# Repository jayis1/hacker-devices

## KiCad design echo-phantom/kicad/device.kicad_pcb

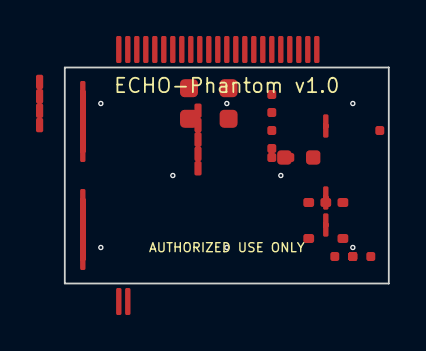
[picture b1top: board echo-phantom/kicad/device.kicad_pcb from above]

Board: 4 copper layers, 18.0 x 12.0 mm, 12 parts (0 on the bottom side), 19 nets, no tracks yet.

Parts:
C1: 100nF; C_0402_1005Metric
C2: 10uF; C_0603_1608Metric
D1: Red; LED_0402_1005Metric
D2: Blue; LED_0402_1005Metric
J1: Target I²S; Hirose_FH12-6S-0.5SH_1x06-1MP_P0.50mm_Horizontal
J2: Host I²S; Hirose_FH12-6S-0.5SH_1x06-1MP_P0.50mm_Horizontal
J3: USB-C; USB_C_Receptacle_GCT_USB4105
U1: STM32H743VIT6; LQFP-100_14x14mm_P0.5mm
U2: BT840F; Fanstel_BT840F
U3: IS42S16160G; TSOP-II-54_10.16x22.22mm_P0.8mm
U4: TLV75533; SOT-23-5
Y1: 25 MHz; Crystal_SMD_3225-4Pin_3.2x2.5mm

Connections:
BLE_RX: U1.PA10, U2.UART_TX
BLE_TX: U1.PA9, U2.UART_RX
FMC_D0: U1.PD14, U3.DQ0
FMC_D1: U1.PD15, U3.DQ1
GND: C1.2, C2.2, D1.2, D2.2, J1.5, J2.5, J3.A1, J3.B12, U1.2, U1.VSS1, U2.GND, U3.VSS1, U4.2, Y1.3
LED_BLUE: D2.1, U1.PB1
LED_RED: D1.1, U1.PB0
SAI1_BCLK_H: J2.1, U1.PB10
SAI1_BCLK_T: J1.1, U1.PA8
SAI1_MCLK_H: J2.4, U1.PC14
SAI1_MCLK_T: J1.4, U1.PC7
SAI1_SD_H: J2.3, U1.PE6
SAI1_SD_T: J1.3, U1.PB3
SAI1_WS_H: J2.2, U1.PF4
SAI1_WS_T: J1.2, U1.PA7
USB_DM: J3.A7, U1.PA11
USB_DP: J3.A6, U1.PA12
VBUS: J3.A4, J3.B9, U4.1, U4.3
VCC_3V3: C1.1, C2.1, J1.6, J2.6, U1.1, U1.VDD1, U2.VDD, U3.VDD1, U4.4, U4.5

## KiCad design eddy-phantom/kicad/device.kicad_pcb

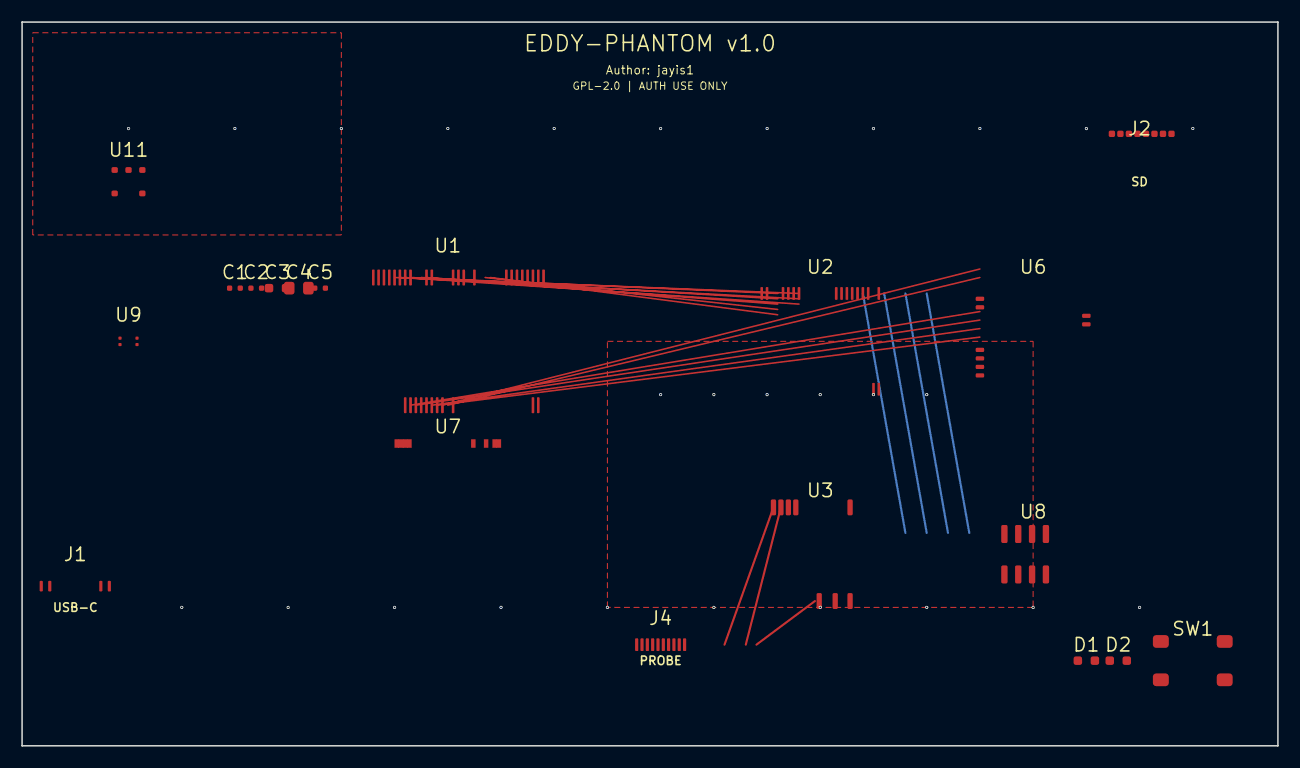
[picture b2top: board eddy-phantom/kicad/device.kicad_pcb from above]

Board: 2 copper layers, 118.0 x 68.0 mm, 19 parts (0 on the bottom side), 28 nets.

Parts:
C1, C2, C5: 100nF; C_0402_1005Metric
C3: 4.7uF; C_0603_1608Metric
C4: 10uF; C_0805_2012Metric
D1: LED_STATUS; LED_0603_1608Metric
D2: LED_CAPTURE; LED_0603_1608Metric
J1: USB-C; USB_C_Receptacle_HRO_TYPE-C-31-M-12
J2: Micro_SD; microSD_HC_Hirose_DM3AT-SF-PEJ521
J4: PROBE_ARRAY; Hirose_FH12-10S-0.5SH
SW1: BTN_ARM; SW_Push_SPST_SKQG_WithStem
U1: STM32H743VIT6; LQFP-100_14x14mm_P0.5mm
U2: AD7606C-6; LQFP-64_10x10mm_P0.5mm
U3: AD8331; SOIC-16_3.9x9.9mm_P1.27mm
U6: NINA-B306; ublox_NINA-B3
U7: IS42S32800G; TSOP-II-54_10.16x22.22mm_P0.8mm
U8: W25Q128JVSIQ; SOIC-8_3.9x4.9mm_P1.27mm
U9: TPS62743; VQFN-8_1.5x1.5mm_P0.4mm
U11: MCP73831; SOT-23-5

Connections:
+3V3: C1.1, C2.1, C3.1, J2.5, U1.1, U1.3, U2.40, U6.1, U7.1, U8.7, U8.8, U9.3
ADC_BUSY: U1.26, U2.27
ADC_CONVST: U1.18, U2.26
ADC_CS_N: U1.16, U2.25
ADC_RANGE: U1.27, U2.30
ADC_RST_N: U1.17, U2.28
AGND: C5.2, J4.2, J4.4, J4.6, J4.8, J4.10, U2.1, U3.2, U3.16
AVDD: C5.1, J4.9, U2.2, U3.3, U3.8
BLE_BOOT: U1.61, U6.24
BLE_CTS: U1.58, U6.11
BLE_RESET_N: U1.60, U6.23
BLE_RTS: U1.59, U6.12
BTN_ARM: SW1.1, SW1.3, U1.30
GND: C1.2, C2.2, C3.2, C4.2, D1.2, D2.2, J1.A1, J1.B1, J2.4, SW1.2, SW1.4, U1.2, U1.4, U2.41, U6.2, U7.2, U8.4, U9.2, U9.4, U11.2
LED_CAPTURE: D2.1, U1.29
LED_STATUS: D1.1, U1.28
PROBE_1_IN: J4.1, U3.1
PROBE_2_IN: J4.3, U3.14
QSPI_NCS: U1.39, U8.1
SPI1_MISO: U1.6, U2.23
SPI1_MOSI: U1.7, U2.24
SPI1_SCK: U1.5, U2.22
SPI4_MOSI: J2.1, J2.2, J2.3
SPI4_SCK: J2.6, U1.8
USART3_RX: U1.57, U6.10
USART3_TX: U1.56, U6.9
VBAT: C4.1, U9.1, U11.3
VUSB: J1.A4, J1.B4, U11.4, U11.5

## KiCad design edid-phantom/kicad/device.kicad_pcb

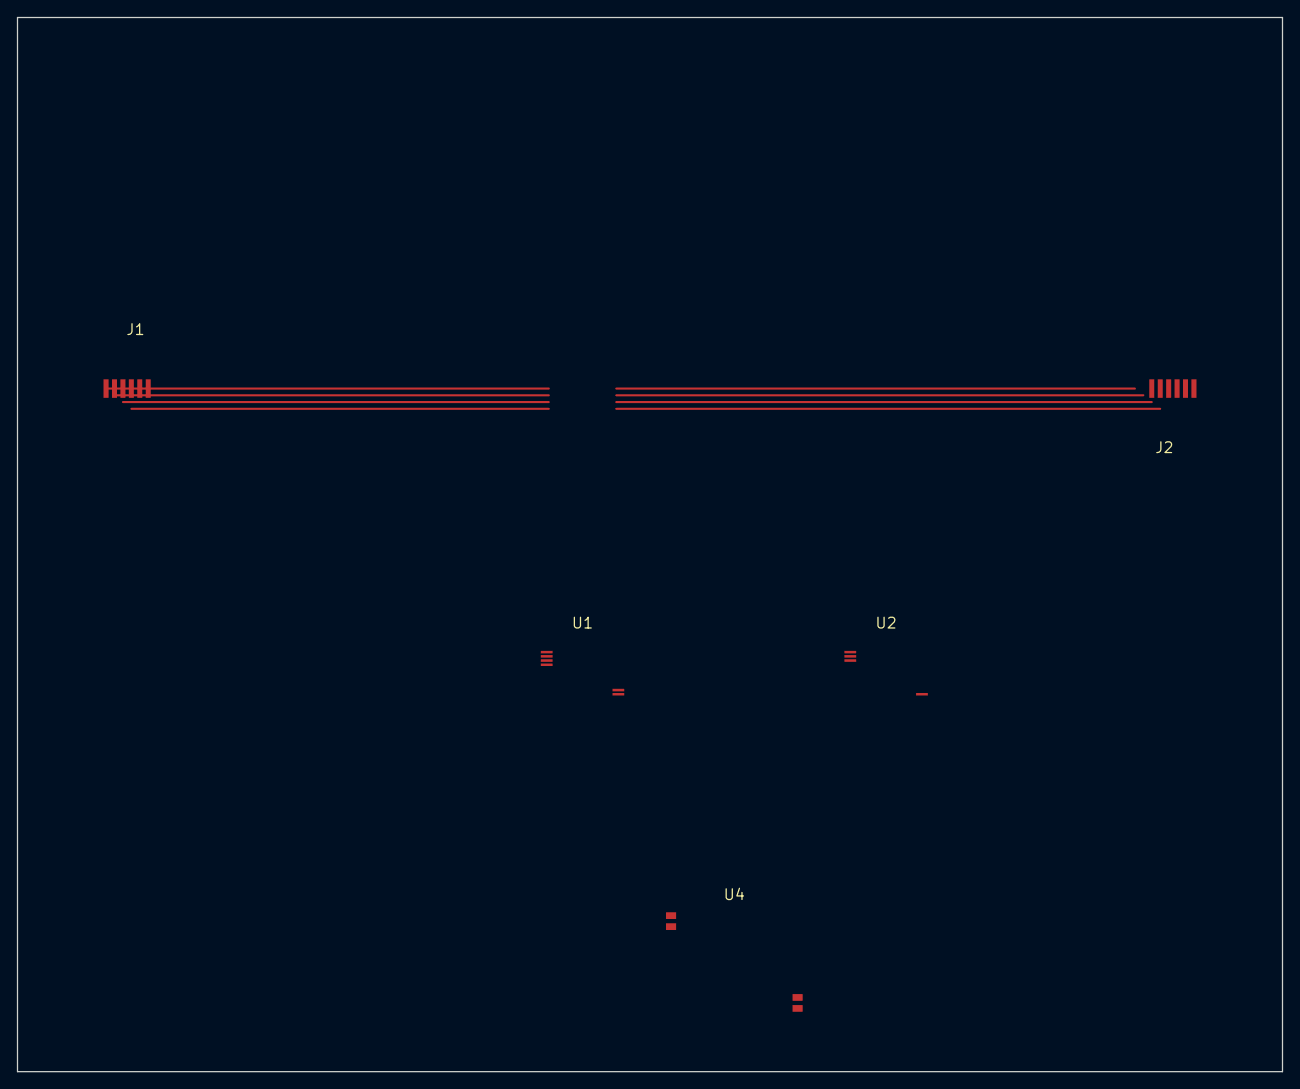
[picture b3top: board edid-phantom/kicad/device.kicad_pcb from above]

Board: 2 copper layers, 150.0 x 125.0 mm, 5 parts (0 on the bottom side), 7 nets.

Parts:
J1: HDMI_Source; HDMI_A_Molex_47151-1001
J2: HDMI_Sink; HDMI_A_Molex_47151-1001
U1: RP2350B; TQFP-48_7x7mm_P0.5mm
U2: iCE40UP5K; TQFP-48_7x7mm_P0.5mm
U4: ESP32-C6-WROOM-1

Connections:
+3V3: U1.40, U4.28
+5V: J1.18, J2.18
CEC_BUS: J1.13, J2.13, U1.4
DDC_SCL: J1.15, J2.15, U1.2, U2.2
DDC_SDA: J1.16, J2.16, U1.1, U2.1
GND: J1.17, J2.17, U1.41, U2.48, U4.29
HPD_PATH: J1.19, J2.19, U1.3, U2.3

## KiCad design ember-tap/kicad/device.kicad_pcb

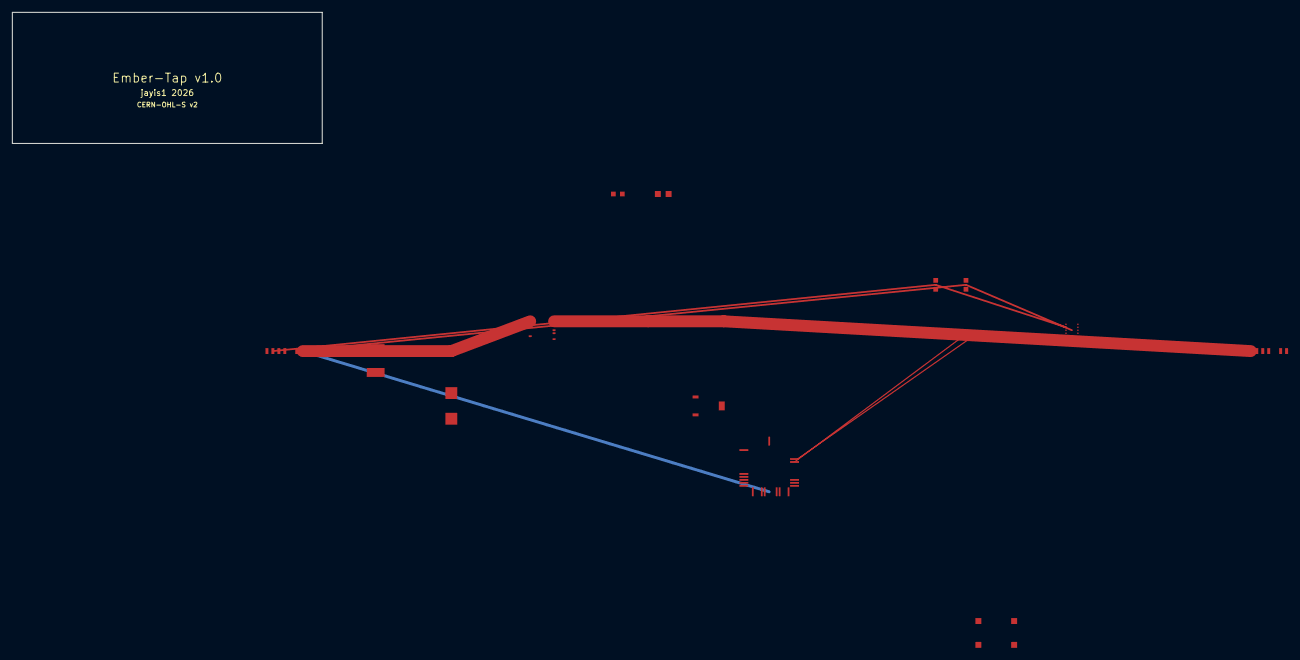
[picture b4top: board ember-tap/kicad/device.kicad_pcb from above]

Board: 2 copper layers, 52.0 x 22.0 mm, 13 parts (0 on the bottom side), 16 nets.

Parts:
C1: 100nF; C_0603
C2: 4.7uF; C_0805
D1: SMBJ24A; D_SMB
F1: MF-MSMF200; Fuse_1812
J1: USB4175; USB_C_Plug_Molex_2175
J2: USB4177; USB_C_Receptacle_Molex_2177
Q1: Si4410BDY; PowerPAK-8
R1, R2: 5k1; R_0603
U1: STM32G474CBT6; LQFP-48_7x7mm_P0.5mm
U2: FUSB302B
U3: TPS25982; VQFN-16
U5: SSD1306; SSD1306_128x64

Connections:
+3V3: C1.1, C2.1, U1.1, U2.A1, U2.B4, U5.1
CC1: J1.A5, J2.A5, R1.1, U2.A2
CC2: J1.B5, J2.B5, R2.1, U2.A3
D+: J1.A6, J2.A6, U1.22
D-: J1.A7, J2.A7, U1.21
FUSB_INT: U1.18, U2.B1
GLITCH_GATE: Q1.1, U1.33
GND: C1.2, C2.2, D1.2, J1.A12, J2.A12, Q1.2, R1.2, R2.2, U1.47, U2.A4, U3.13, U5.2
I2C1_SCL: U1.42, U2.B2, U3.16
I2C1_SDA: U1.43, U2.B3, U3.15
I2C2_SCL: U1.29, U5.3
I2C2_SDA: U1.30, U5.4
TPS_EN: U1.35, U3.3
TPS_FLTB: U1.34, U3.6
VBUS_IN: D1.1, F1.1, F1.2, J1.A4, U3.1
VBUS_OUT: J2.A4, Q1.3, U3.9

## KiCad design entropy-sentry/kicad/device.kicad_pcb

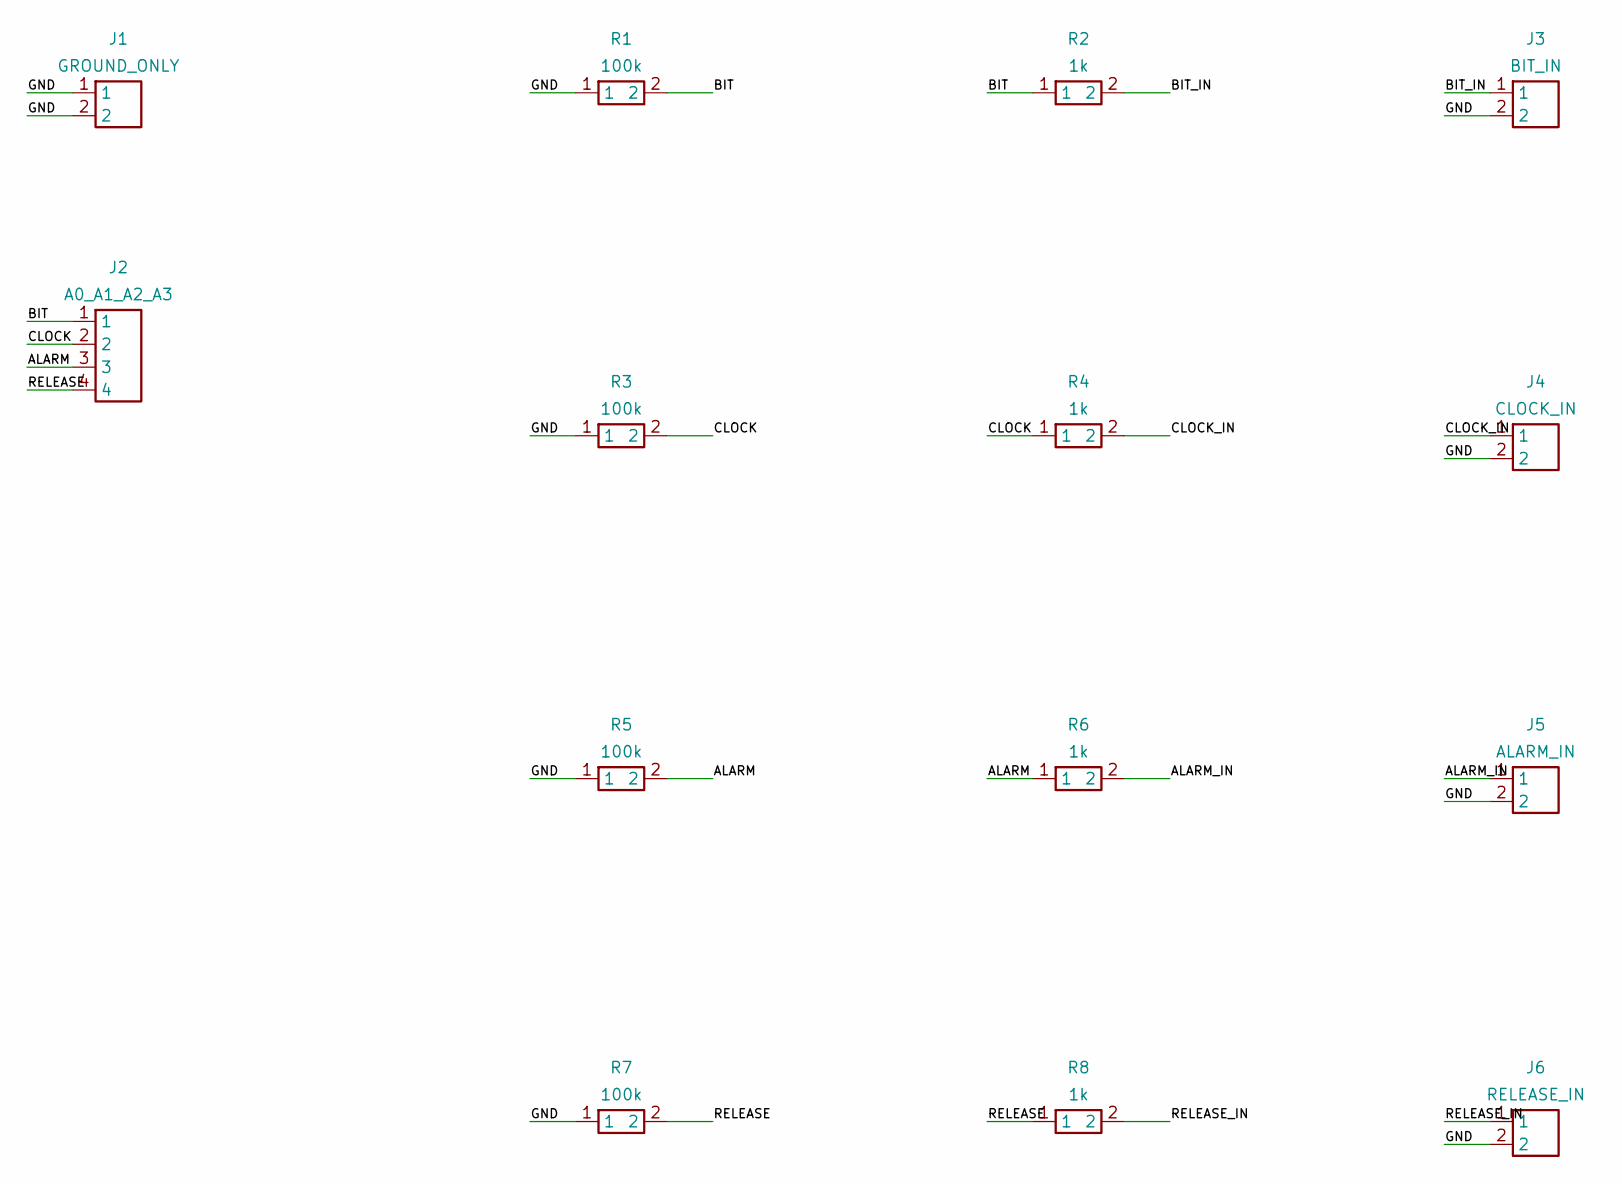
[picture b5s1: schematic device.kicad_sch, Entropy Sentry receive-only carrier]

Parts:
J1: GROUND_ONLY; PinHeader_1x02_P2.54mm_Vertical
J2: A0_A1_A2_A3; PinHeader_1x04_P2.54mm_Vertical
J3: BIT_IN; PinHeader_1x02_P2.54mm_Vertical
J4: CLOCK_IN; PinHeader_1x02_P2.54mm_Vertical
J5: ALARM_IN; PinHeader_1x02_P2.54mm_Vertical
J6: RELEASE_IN; PinHeader_1x02_P2.54mm_Vertical
R1, R3, R5, R7: 100k; R_Axial_DIN0207_L6.3mm_D2.5mm_P7.62mm_Horizontal
R2, R4, R6, R8: 1k; R_Axial_DIN0207_L6.3mm_D2.5mm_P7.62mm_Horizontal

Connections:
ALARM: J2.3, R5.2, R6.1
ALARM_IN: J5.1, R6.2
BIT: J2.1, R1.2, R2.1
BIT_IN: J3.1, R2.2
CLOCK: J2.2, R3.2, R4.1
CLOCK_IN: J4.1, R4.2
GND: J1.1, J1.2, J3.2, J4.2, J5.2, J6.2, R1.1, R3.1, R5.1, R7.1
RELEASE: J2.4, R7.2, R8.1
RELEASE_IN: J6.1, R8.2

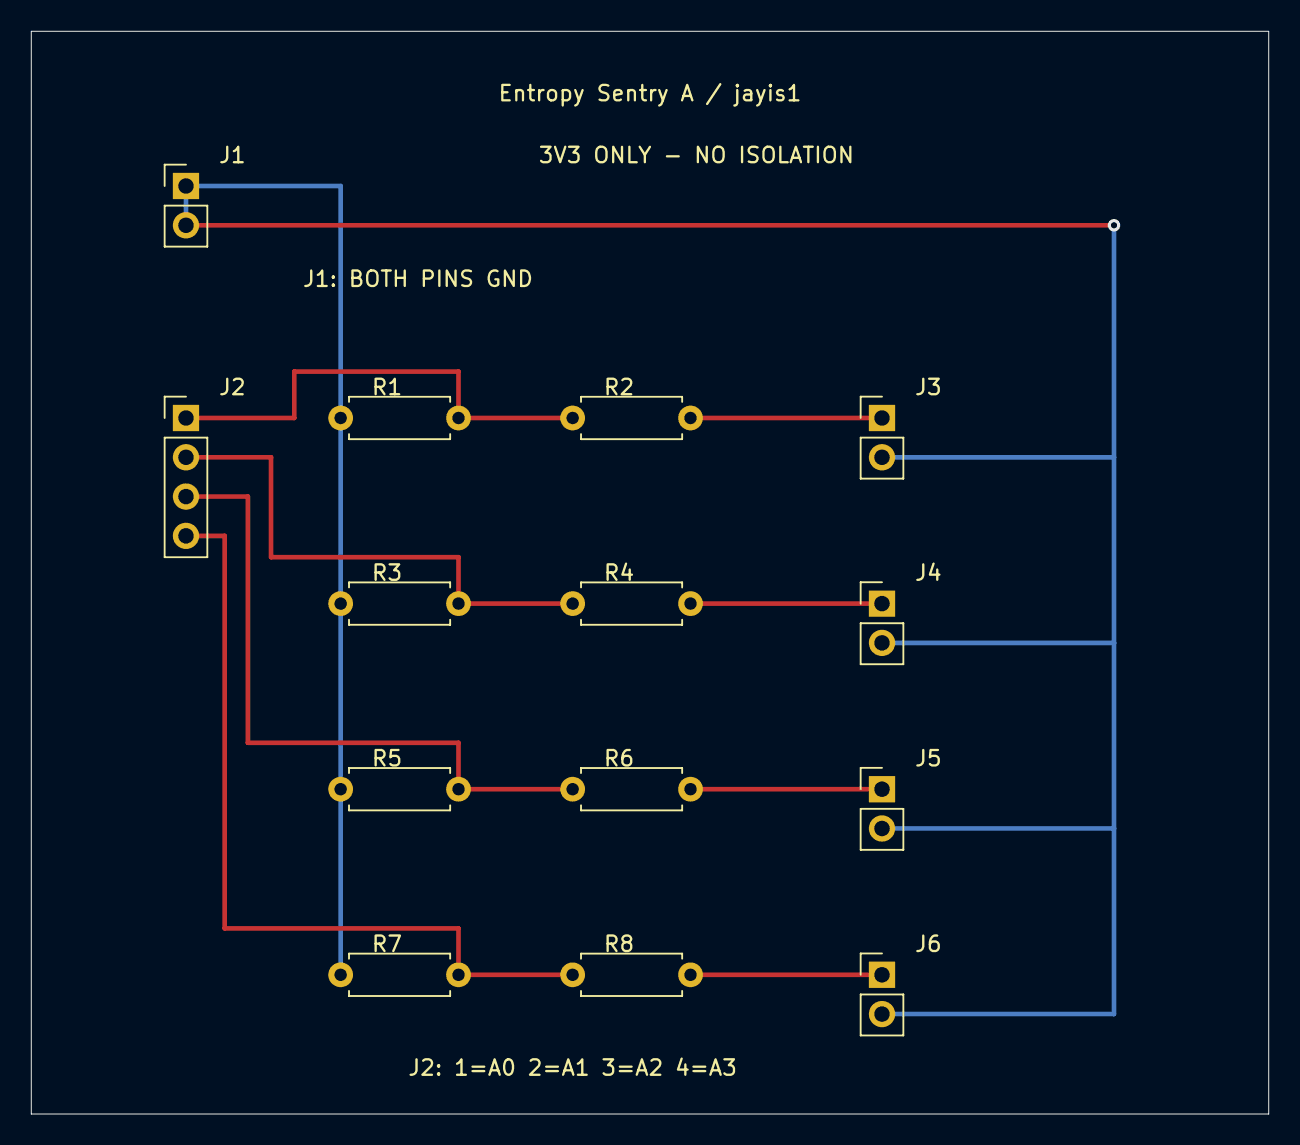
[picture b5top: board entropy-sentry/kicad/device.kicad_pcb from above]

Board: 2 copper layers, 80.0 x 70.0 mm, 14 parts (0 on the bottom side), 9 nets.

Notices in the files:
echo-phantom/kicad/device.kicad_sch:
License: CERN-OHL-S v2
Author: jayis1 — License: CERN-OHL-S v2
eddy-phantom/kicad/device.kicad_pcb:
License: GPL-2.0
GPL-2.0 | AUTH USE ONLY
edid-phantom/kicad/device.kicad_pcb:
Copyright (c) 2026 jayis1
ember-tap/kicad/device.kicad_pcb:
CERN-OHL-S v2
